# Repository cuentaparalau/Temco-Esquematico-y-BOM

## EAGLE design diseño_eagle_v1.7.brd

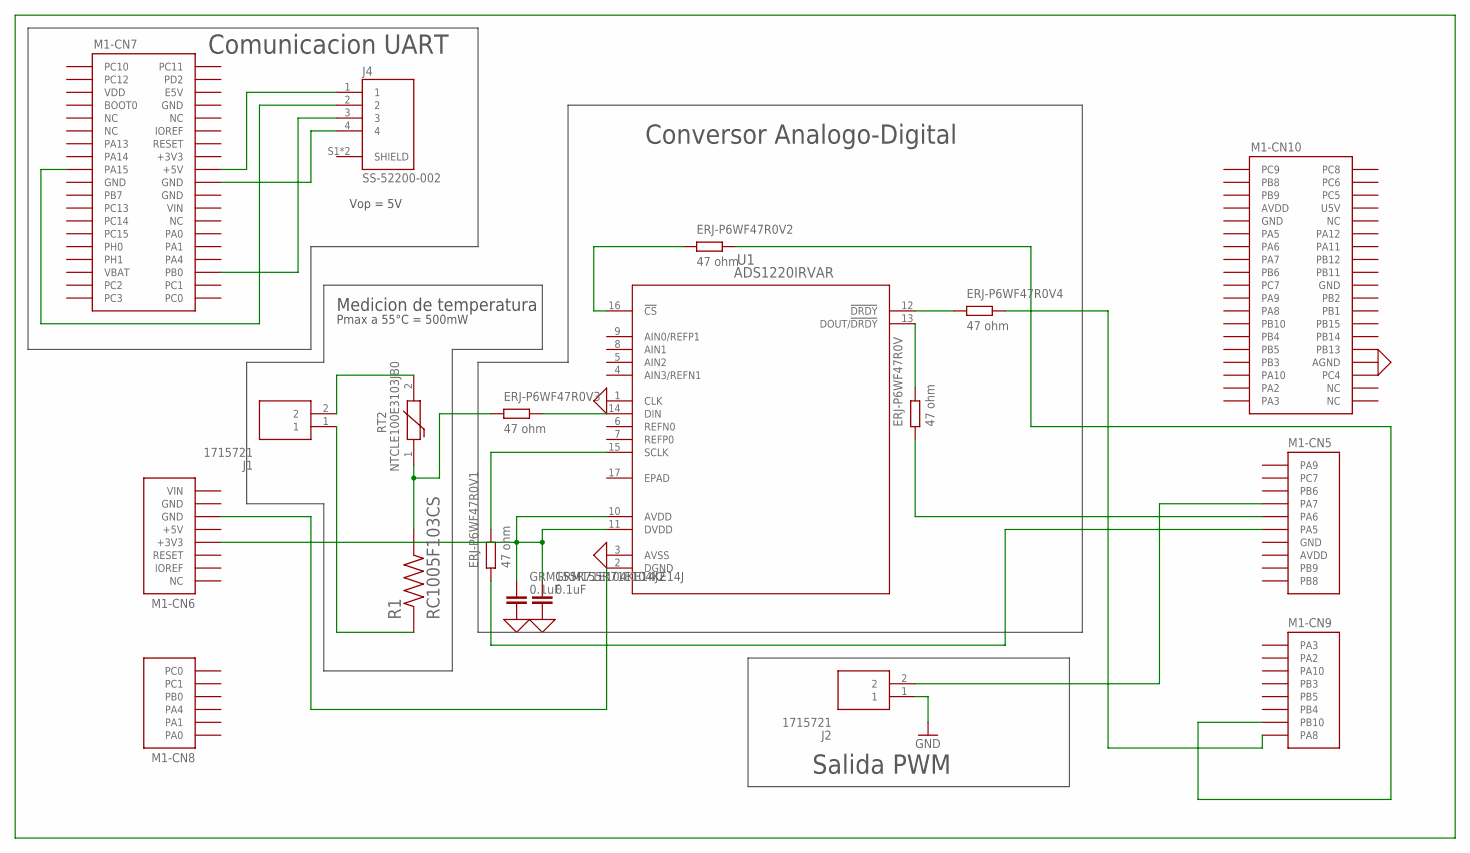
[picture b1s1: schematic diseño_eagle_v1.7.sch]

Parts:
J1, J2: 1715721
J4: SS-52200-002; BEL_SS-52200-002
M1: NUCLEO-L452RE; NUCLEO-64
R1: RC1005F103CS; RESC1005X40N
RT2: NTCLE100E3103JB0
U1: ADS1220IRVAR; RVA16_2P14X2P14

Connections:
0: M1.CN10-32 (AGND), U1.1 (CLK), U1.3 (AVSS)
+3V3: M1.CN7-16 (+3V3)
+5V: M1.CN6-5 (+5V)
AVDD: M1.CN5-8 (AVDD), M1.CN10-7 (AVDD)
GND: J2.1, M1.CN5-7 (GND), M1.CN6-7 (GND), M1.CN7-8 (GND), M1.CN7-19 (GND), M1.CN7-22 (GND), M1.CN10-9 (GND), M1.CN10-20 (GND)
IOREF: M1.CN6-2 (IOREF)
unnamed: J4.1, M1.CN7-18 (+5V)
unnamed: R1.2, RT2.1
unnamed: M1.CN6-4 (+3V3), U1.10 (AVDD), U1.11 (DVDD)
unnamed: M1.CN6-6 (GND), U1.2 (DGND)
unnamed: J1.2, RT2.2
unnamed: J4.2, M1.CN7-17 (PA15)
unnamed: J1.1, R1.1
unnamed: J4.4, M1.CN7-20 (GND)
unnamed: J4.3, M1.CN7-34 (PB0)
unnamed: J2.2, M1.CN5-4 (PA7)
U5V: M1.CN10-8 (U5V)
VBAT: M1.CN7-33 (VBAT)
VDD: M1.CN7-5 (VDD)
VIN: M1.CN6-8 (VIN), M1.CN7-24 (VIN)

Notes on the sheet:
Comunicacion UART
Salida PWM
Medicion de temperatura
Conversor Analogo-Digital
Vop = 5V
Pmax a 55°C = 500mW

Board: 2 copper layers, 7 parts (0 on the bottom side), 14 nets, no tracks yet.

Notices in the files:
parts and their libraries:
COPYRIGHT: Copyright (C) 2023 Ultra Librarian. All rights reserved.
